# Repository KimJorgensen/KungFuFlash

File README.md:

# Kung Fu Flash

Project is moved to https://codeberg.org/KimJorgensen/KungFuFlash

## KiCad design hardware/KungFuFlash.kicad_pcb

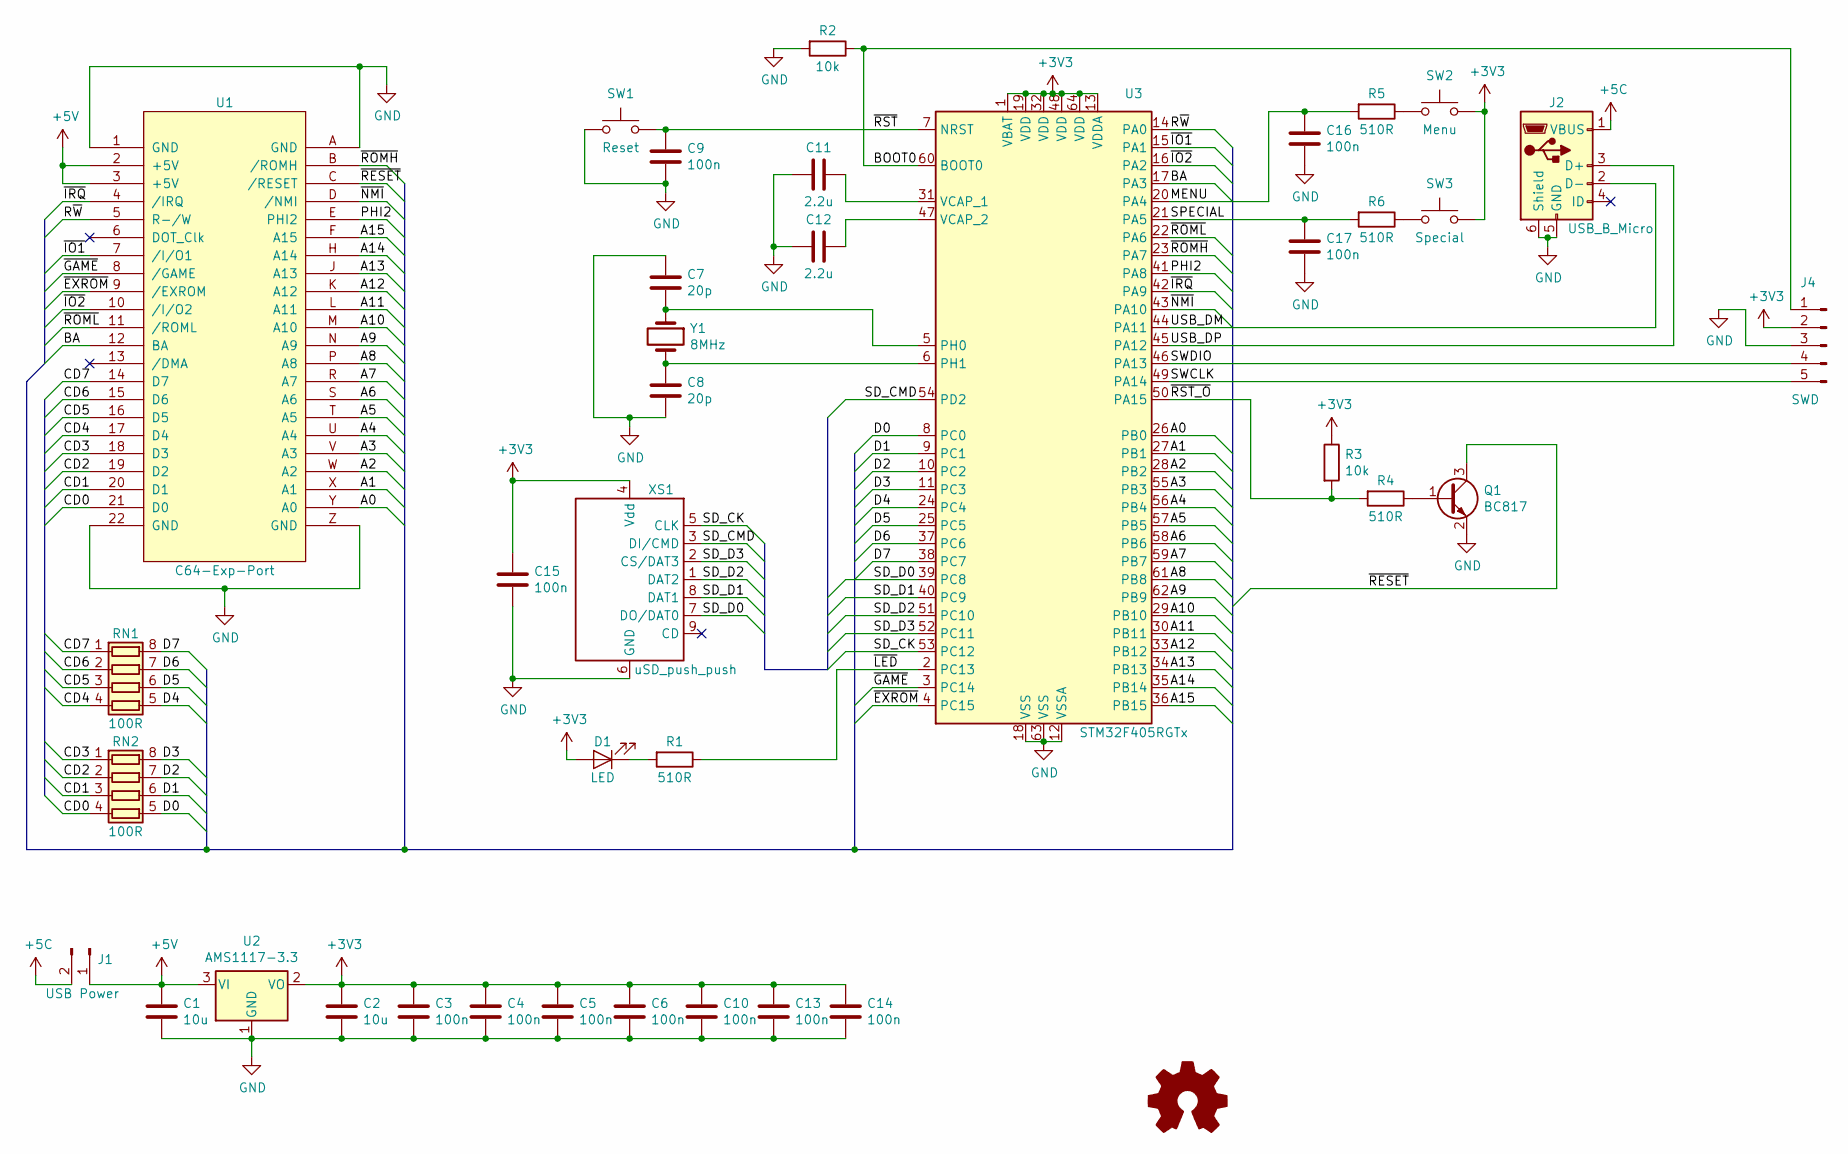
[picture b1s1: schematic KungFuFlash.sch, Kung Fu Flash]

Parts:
C1, C2: 10u; C_0805_2012Metric_Pad1.15x1.40mm_HandSolder
C3, C4, C5, C6, C9, C10, C13, C14, C15, C16, C17: 100n; C_0603_1608Metric_Pad1.05x0.95mm_HandSolder
C7, C8: 20p; C_0603_1608Metric_Pad1.05x0.95mm_HandSolder
C11, C12: 2.2u; C_0805_2012Metric_Pad1.15x1.40mm_HandSolder
D1: LED; LED_0805_2012Metric_Pad1.15x1.40mm_HandSolder
J1: USB Power; PinHeader_1x02_P2.54mm_Vertical
J2: USB_B_Micro; Conn_USBmicro-B_ebay-side_TH
J4: SWD; PinHeader_1x05_P2.54mm_Vertical
Q1: BC817; SOT-23
R1, R4, R5, R6: 510R; R_0805_2012Metric_Pad1.15x1.40mm_HandSolder
R2, R3: 10k; R_0805_2012Metric_Pad1.15x1.40mm_HandSolder
RN1, RN2: 100R; R_Array_Convex_4x0603
SW1: Reset; SW_PUSH_6mm_H8mm
SW2: Menu; SW_PUSH_6mm_H8mm
SW3: Special; SW_PUSH_6mm_H8mm
U1: C64-Exp-Port; C64-Cart
U2: AMS1117-3.3; SOT-223-3_TabPin2
U3: STM32F405RGTx; LQFP-64_10x10mm_P0.5mm
XS1: uSD_push_push; Conn_uSDcard
Y1: 8MHz; Crystal_SMD_5032-2Pin_5.0x3.2mm

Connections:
+3V3: C2.1, C3.1, C4.1, C5.1, C6.1, C10.1, C13.1, C14.1, C15.1, D1.2 (A), J4.2, R3.1, SW2.1, SW3.1, U2.2 (VO), U3.1 (VBAT), U3.13 (VDDA), U3.19 (VDD), U3.32 (VDD), U3.48 (VDD), U3.64 (VDD), XS1.4 (Vdd)
+5C: J1.2, J2.1 (VBUS)
+5V: C1.1, J1.1, U1.2 (+5V), U1.3 (+5V), U2.3 (VI)
/A0: U1.Y (A0), U3.26 (PB0)
/A1: U1.X (A1), U3.27 (PB1)
/A2: U1.W (A2), U3.28 (PB2)
/A3: U1.V (A3), U3.55 (PB3)
/A4: U1.U (A4), U3.56 (PB4)
/A5: U1.T (A5), U3.57 (PB5)
/A6: U1.S (A6), U3.58 (PB6)
/A7: U1.R (A7), U3.59 (PB7)
/A8: U1.P (A8), U3.61 (PB8)
/A9: U1.N (A9), U3.62 (PB9)
/A10: U1.M (A10), U3.29 (PB10)
/A11: U1.L (A11), U3.30 (PB11)
/A12: U1.K (A12), U3.33 (PB12)
/A13: U1.J (A13), U3.34 (PB13)
/A14: U1.H (A14), U3.35 (PB14)
/A15: U1.F (A15), U3.36 (PB15)
/BA: U1.12 (BA), U3.17 (PA3)
/BOOT0: J4.1, R2.1, U3.60 (BOOT0)
/CD0: RN2.4 (R4.1), U1.21 (D0)
/CD1: RN2.3 (R3.1), U1.20 (D1)
/CD2: RN2.2 (R2.1), U1.19 (D2)
/CD3: RN2.1 (R1.1), U1.18 (D3)
/CD4: RN1.4 (R4.1), U1.17 (D4)
/CD5: RN1.3 (R3.1), U1.16 (D5)
/CD6: RN1.2 (R2.1), U1.15 (D6)
/CD7: RN1.1 (R1.1), U1.14 (D7)
/D0: RN2.5 (R4.2), U3.8 (PC0)
/D1: RN2.6 (R3.2), U3.9 (PC1)
/D2: RN2.7 (R2.2), U3.10 (PC2)
/D3: RN2.8 (R1.2), U3.11 (PC3)
/D4: RN1.5 (R4.2), U3.24 (PC4)
/D5: RN1.6 (R3.2), U3.25 (PC5)
/D6: RN1.7 (R2.2), U3.37 (PC6)
/D7: RN1.8 (R1.2), U3.38 (PC7)
/MENU: C16.1, R5.2, U3.20 (PA4)
/PHI2: U1.E (PHI2), U3.41 (PA8)
/R~W: U1.5 (R-/W), U3.14 (PA0)
/SD_CK: U3.53 (PC12), XS1.5 (CLK)
/SD_CMD: U3.54 (PD2), XS1.3 (DI/CMD)
/SD_D0: U3.39 (PC8), XS1.7 (DO/DAT0)
/SD_D1: U3.40 (PC9), XS1.8 (DAT1)
/SD_D2: U3.51 (PC10), XS1.1 (DAT2)
/SD_D3: U3.52 (PC11), XS1.2 (CS/DAT3)
/SPECIAL: C17.1, R6.2, U3.21 (PA5)
/SWCLK: J4.5, U3.49 (PA14)
/SWDIO: J4.4, U3.46 (PA13)
/USB_DM: J2.2 (D-), U3.44 (PA11)
/USB_DP: J2.3 (D+), U3.45 (PA12)
/~EXROM: U1.9 (/EXROM), U3.4 (PC15)
/~GAME: U1.8 (/GAME), U3.3 (PC14)
/~IO1: U1.7 (/I/O1), U3.15 (PA1)
/~IO2: U1.10 (/I/O2), U3.16 (PA2)
/~IRQ: U1.4 (/IRQ), U3.42 (PA9)
/~LED: R1.1, U3.2 (PC13)
/~NMI: U1.D (/NMI), U3.43 (PA10)
/~RESET: Q1.3 (C), U1.C (/RESET)
/~ROMH: U1.B (/ROMH), U3.23 (PA7)
/~ROML: U1.11 (/ROML), U3.22 (PA6)
/~RST: C9.1, SW1.2, U3.7 (NRST)
/~RST_O: R3.2, R4.2, U3.50 (PA15)
GND: C1.2, C2.2, C3.2, C4.2, C5.2, C6.2, C7.1, C8.2, C9.2, C10.2, C11.1, C12.2, C13.2, C14.2, C15.2, C16.2, C17.2, J2.5 (GND), J2.6 (Shield), J4.3, Q1.2 (E), R2.2, SW1.1, U1.1 (GND), U1.22 (GND), U1.A (GND), U1.Z (GND), U2.1 (GND), U3.12 (VSSA), U3.18 (VSS), U3.63 (VSS), XS1.6 (GND)
unnamed: C7.2, U3.5 (PH0), Y1.1
unnamed: C8.1, U3.6 (PH1), Y1.2
unnamed: C11.2, U3.31 (VCAP_1)
unnamed: C12.1, U3.47 (VCAP_2)
unnamed: D1.1 (K), R1.2
unnamed: Q1.1 (B), R4.1
unnamed: R5.1, SW2.2
unnamed: R6.1, SW3.2

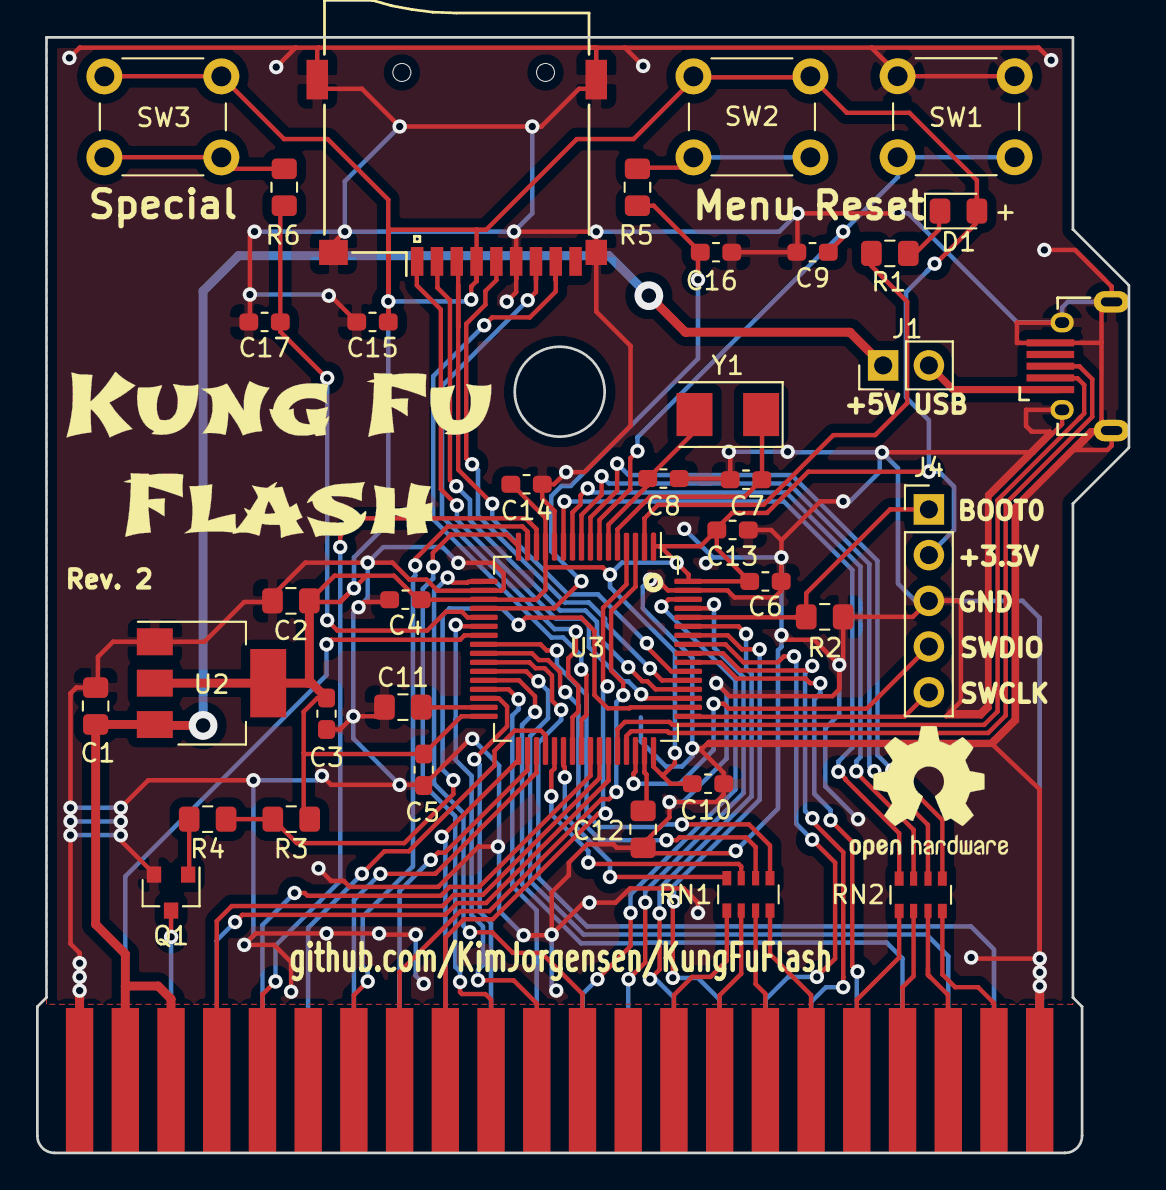
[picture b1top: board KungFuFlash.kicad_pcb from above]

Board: 2 copper layers, 60.6 x 62.0 mm, 38 parts (0 on the bottom side), 72 nets.

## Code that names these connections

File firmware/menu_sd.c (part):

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                 memcmp("CBM", &dat_buffer[0x4007], 3) == 0))
            {
                dat_file.crt.type = CRT_C128_NORMAL_CARTRIDGE;
                dat_file.crt.exrom = 1;
                dat_file.crt.game = 1;

                if (!crt_is_supported(dat_file.crt.type))
                {
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            else if (len && len <= 16*1024)
            {
                dat_file.crt.type = CRT_NORMAL_CARTRIDGE;
                dat_file.crt.exrom = 0;
                dat_file.crt.game = 0;
                // Look for C64 CRT identifier "CBM80"
                if (memcmp("\xc3""\xc2""\xcd""80", &dat_buffer[0x0004], 5) == 0)
                {
                    if (len <= 8*1024)
                    {
                        dat_file.crt.game = 1;
                    }
                }
                else    // Assume Ultimax
                {
                    dat_file.crt.exrom = 1;
                    // Mirror the first 4k
                    if (len <= 4*1024)
                    {
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    return sd_handle_change_dir(state, "..", true);
}

static const MENU sd_menu = {
    .state = &sd_state,
    .dir = (u8 (*)(void *))sd_handle_dir,
    .dir_up = (u8 (*)(void *, bool))sd_handle_dir_up,
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    .select = (u8 (*)(void *, u8, u8))sd_handle_select
};

static const MENU *sd_menu_init(void)
{
    chdir_last();
    sd_state.page_no = 0;
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
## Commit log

2019-12-27 Add Windows build
2020-01-03 Add missing lib files
2020-01-19 Accept non-standard CRT header length
2020-01-19 Add Fun Play/Power Play support
2020-01-19 Add Dinamic CRT support
2020-01-24 Add pink cartridge
2020-01-24 Update pcb picture. Thanks bigby
2020-01-24 Use new cartridge picture
2020-02-08 Add ROM file type
2020-02-08 Add KCS Power Cartridge support
2020-02-08 KCS Power Cartridge support
2020-02-09 Add link to cartridge case by bigby
2020-02-11 Added support for the Super Zaxxon cartridge
2020-02-11 Properly sorted cartridge types and optimized read_handler performance.
2020-02-12 Add Zaxxon + Super Zaxxon support
2020-02-14 Add file options and settings menu
2020-02-28 Add disk drive emulation based on disk2easyflash
2020-02-28 Calculate blocks free
2020-02-29 Add D71 and D81 support
2020-04-05 Better error text. Thanks tulan
2020-04-09 Support for reading SEQ files
2020-04-09 Add P00 support
2020-04-11 Performance optimization
2020-04-11 Don't enter low-power mode
2020-04-11 Don't use SysTick interrupt
2020-04-11 Correct flag clear on timer status register
2020-04-13 Minor code clean-up
2020-04-14 Use timer compare to detect end of clock cycle
2020-04-26 Update with links to gerbers, BOM and firmware
2020-04-26 Fix links
2020-05-22 PCB rev. 2
2020-06-15 Performance optimizations and timing adjustments
2020-06-15 Allow to start Jumpman Junior from Launcher
2020-07-05 Add missing files to compile
2020-07-07 Speed up turbo image write from PC to 1541 by introducing write interleave parameter
2020-07-08 flush stdout after printf (linux terminal seems picky about that) and some tidy up
2020-07-12 Support latest 64tass compiler
2020-07-12 Update ef3usb.prg binary
2020-07-12 ef3usb Windows build
2020-07-12 Link to rev. 2 of gerber files
2020-07-23 EF_RAM resident area refactored to make room for save functions and longer filename
2020-07-30 Fix bug in directory listing
2020-07-30 Add limited EAPI support
2020-08-01 EAPI write support for bank 0-7
2020-08-02 Option for saving updated EF CRT
2020-08-02 Add detection of KFF in EAPI driver
2020-08-02 Don't write empty CHIP to CRT file
2020-08-04 Fix detection of EAPI write done
2020-08-05 Basic SAVE implementation
2020-08-05 blink debug routine removed
2020-08-05 Option for saving CRT as new file
2020-08-06 Option for deleting file
2020-08-17 curly brace typos, constants naming, overwrite parse fixed, unified c compile unit restored, debug (dead) codes removed
2020-08-17 RECV_BUFFER_OFFSET renamed to SAVE... and moved to commands.h, unnecessary disable_ef_rom copies are eliminated
2020-08-17 further curly braces cosmetic fixes
2020-08-17 c64_interface check made more robust (4 chars DONE instead of 2 chars OK)
2020-08-17 Waiting for "done" is optimized for size
2020-08-27 Two phase save refactor, DONE is expected by C64, no size check, enhanced 1541 compatibity
2020-08-27 d64_reader/writer merged into d64, fix in disks.s
2020-08-27 Renaming some labels
2020-08-29 Support 1024k Magic Desk cartridges
2020-08-31 refactored d64 and drive api communication
2020-09-03 Recommended SWD
2020-09-04 Basic SAVE routine (#30)
    * Basic SAVE implementation
    * EF_RAM resident area refactored to make room for save functions and longer filename
    * curly brace typos, constants naming, overwrite parse fixed, unified c compile unit restored, debug (dead) codes removed
    * RECV_BUFFER_OFFSET renamed to SAVE... and moved to commands.h, unnecessary disable_ef_rom copies are eliminated
    * further curly braces cosmetic fixes
    * c64_interface check made more robust (4 chars DONE instead of 2 chars OK)
2020-11-11 Add compile time option to select which device is used when loading from D64 files. This avoids conflicts with existing drives/SD2IEC devices.
    Use 'make d64devnr=x' to set device to x (4..30 are valid). When omitted it defaults to 8
2020-11-29 D71/D81 save support. Autostart and device number setting
2020-11-29 Disk save (#60)
    * Basic SAVE routine by dikdom
    * D71/D81 save support
    * Autostart and device number setting
2020-11-30 Rearrange magic desk flash usage
2020-12-17 Experiential NTSC support. Performance optimizations using int32
2020-12-19 Updated limitations
2020-12-20 Timing adjustments
2020-12-27 Support JiffyDOS, C64GS, and large PRGs
2020-12-30 Add search feature. Hide dot files
2020-12-30 Adjust filename length
2021-01-13 Added support for Expert Cart and Georam.
2021-01-13 some minor text editting
2021-01-17 Added support for WarpSpeed cartridge
2021-01-18 fixed (I hope) the loading of expert payloads.
2021-01-21 fixed topics found in review
2021-01-24 Added support for WarpSpeed cartridge (#76)
    * Added support for WarpSpeed cartridge
    Authored-by: Sven Oliver Moll
2021-01-27 - Removed Georam per request from Kim Jorgens0n (code is still here and will be re-enabled later) - When expert expansion is active and programmed (the special button toggles between active and inact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
2021-02-04 Fix bug reading 64 kb file using FAT16
2021-02-06 Add freeze machine support
2021-02-06 Update Supported Cartridges
2021-04-10 Code cleanup
2021-04-10 Treat extensionless files as PRG
2021-04-11 Add support for RGCD cartridge
2021-04-24 crt_init cleanup
2021-04-24 Fix broken Fun Play/Power Play cartridge support
2021-04-24 Add Super Games support
2021-04-24 Add Prophet64 support
2021-08-09 Update libusb_stm32 and fix USB race condition
2021-08-12 Add EF3 BBS
2021-08-18 Add C128 cartridge support
2021-08-18 Check for correct fw
2021-09-12 Add Drean cartridge support
2021-09-19 Add simple diagnostic tool
2021-09-19 Minor code cleanup
2021-10-23 Improve detection of C64 clock signal
2021-10-24 Fix broken EasyFlash VIC-II/C128 mode
2021-10-30 Less restrictive frequency check
2021-11-14 Move scratch_buf to CCMRAM and extend to 32kB
2021-11-16 Update auto-generated files
2021-11-29 Combine PAL and NTSC firmware
2021-11-29 Add T64 support (normal tape files only)
2021-12-07 Made menu code more compact
2021-12-10 Code reuse
2021-12-11 Move Normal, EF, and Ocean CRT support to FW
2021-12-16 Move support for more CRTs to FW
2021-12-18 Use typedefs for integer types
2021-12-18 Force inline performance critical functions
2021-12-19 Change compiler optimization and disable module
2021-12-19 Allow FW update for NTSC users
2021-12-19 Add T64. UPD file not required in root dir
2022-01-02 Move launcher memory to $C000
2022-01-02 Fix bug in CLOSE
2022-01-02 Check status when getting byte
2022-01-02 Power-on message
2022-01-02 Correct status
2022-01-02 Support for open $
2022-01-03 Skip load to EF RAM
2022-01-05 Support basic SD2IEC commands
2022-01-07 Fix broken mount D64 option
2022-01-16 Better parsing of dir command
2022-02-10 Support CRT v2.0 and WarpSpeed 128
2022-03-26 Optimize C64/KFF communication
2022-03-26 Reinstall vectors after RUN/STOP RESTORE
2022-03-28 Update libusb_stm32
2022-03-30 Optimize VIC-II reads for ultimax cartridges
2022-04-13 Add information about (phi2) diagnostics to firmware readme - it is difficult for users to find on only one specific release note (v1.27)
2022-04-15 Add information about (phi2) diagnostics to firmware readme - it is difficult for users to find on only one specific release note (v1.27) (#123)
2022-04-25 Optimize SD card access
2022-04-27 Logging cleanup
2022-04-30 Improve disk write support
2022-04-30 Small performance optimizations
2022-05-02 Fix timing problems on some C64s
2022-05-14 Improve search text editor
2022-05-22 Reinstall disk vectors after load
2022-05-26 Support block read/write
2022-05-27 Allow custom vectors
2022-05-27 Cursor placement
2022-06-06 Use COLOR_PURPLE for newer CC65
2022-07-03 Load/save: Clear timer interrupt flags
2022-07-03 Device number can be set to 8-15
2022-07-04 Add support for Pagefox cartridge
2022-09-16 Add support for 128KiB Super Snapshot v5 ROM.
2022-09-16 Support 128k Super Snapshot ROM
2022-09-20 NTSC timing adjustments
2022-10-23 No FPU registers on the stack
2022-10-24 Performance optimizations and phi2 offset feature
2022-10-24 phi2 offset adjustment
2023-07-24 Improve hardware error message
2023-07-25 Support generic cartridge ROM/BIN
2023-07-27 Add text file reader
2023-07-27 Update README.md
    Reformat supported cartridges list
2023-07-28 Add picture of PCB rev. 2
2023-08-07 Fix compiler warnings
2023-08-07 Allow files on SD card to be opened as SEQ
2023-08-08 Make it easier to enable logging
2023-08-08 Capital letter
2023-09-23 Improve emulation of direct access
2023-12-20 Minor documentation changes
2023-12-20 Minor documentation changes (#182)
2024-01-01 Ensure valid C64 clock before selecting NTSC or PAL handler
2024-01-01 Hide hidden and system files/folders
2024-03-09 Reset C64 when USB command is received
2024-03-23 List when the USB port is active
2024-06-30 Support 4k CRT images
2024-06-30 Support MACH 5
2024-08-30 Added support for ROSS cartridge
2024-12-28 Update issue templates
2025-01-04 Fix race condition in menu startup
2025-03-22 Add Ross CRT support (16K and 32K supported) (#202)
    * Added support for ROSS cartridge
    * Update README.md
2025-03-23 Ross 64 kb support
2025-12-18 Project is moved to Codeberg

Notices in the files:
firmware/menu_sd.c:
Copyright (c) 2019-2023 Kim Jørgensen
